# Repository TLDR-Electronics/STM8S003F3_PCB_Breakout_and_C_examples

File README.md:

# STM8S003F3 PCB Breakout and C examples
Breakout board and some lightweight C examples of the STM8S003F3 using the Small Device C Compiler (SDCC). Without the need for the STM8S/A Standard peripheral library.
Some examples are also compatable with the IAR compiler.

Gerbers and design files for low cost breakout boards for the STM8S003F3 are available in the hardware folder.
The breakout boards are designed in EasyEDA and KiCAD are placed in the hardware folder. 
The EasyEDA gerbers and assembly files have been phyically tested with JLCPCB. KiCAD files have not been tested.

## Software Setup
To compile and run this SDCC will need to be installed.
On linux, this can be done with the `sudo apt update` and `sudo apt install sdcc`

## Flashing the STM8
The stm8flash utility is used to program the stm8 devices: https://github.com/vdudouyt/stm8flash 
Make sure you have an compatable ST-LINK programmer
This will need to be compiled. The directory for the executable was placed in:

>/home/*\<your username\>*/tools/stm8flash/

## Make Commands

Typing in the following commands in the development folder:
- `make blink` will compile the blink program to the *./bin/* folder.
- `make tim2` will compile the timer2 interrupt program to the *./bin/* folder.
- `make t2delay` will compile the timer2 delay program to the *./bin/* folder.
- `make burn` command will flash the device depending on the last build.
- `make clean` will clear the binary and the *./bin/* folder.

Depending on your programmer, the makefile may need to be edited.

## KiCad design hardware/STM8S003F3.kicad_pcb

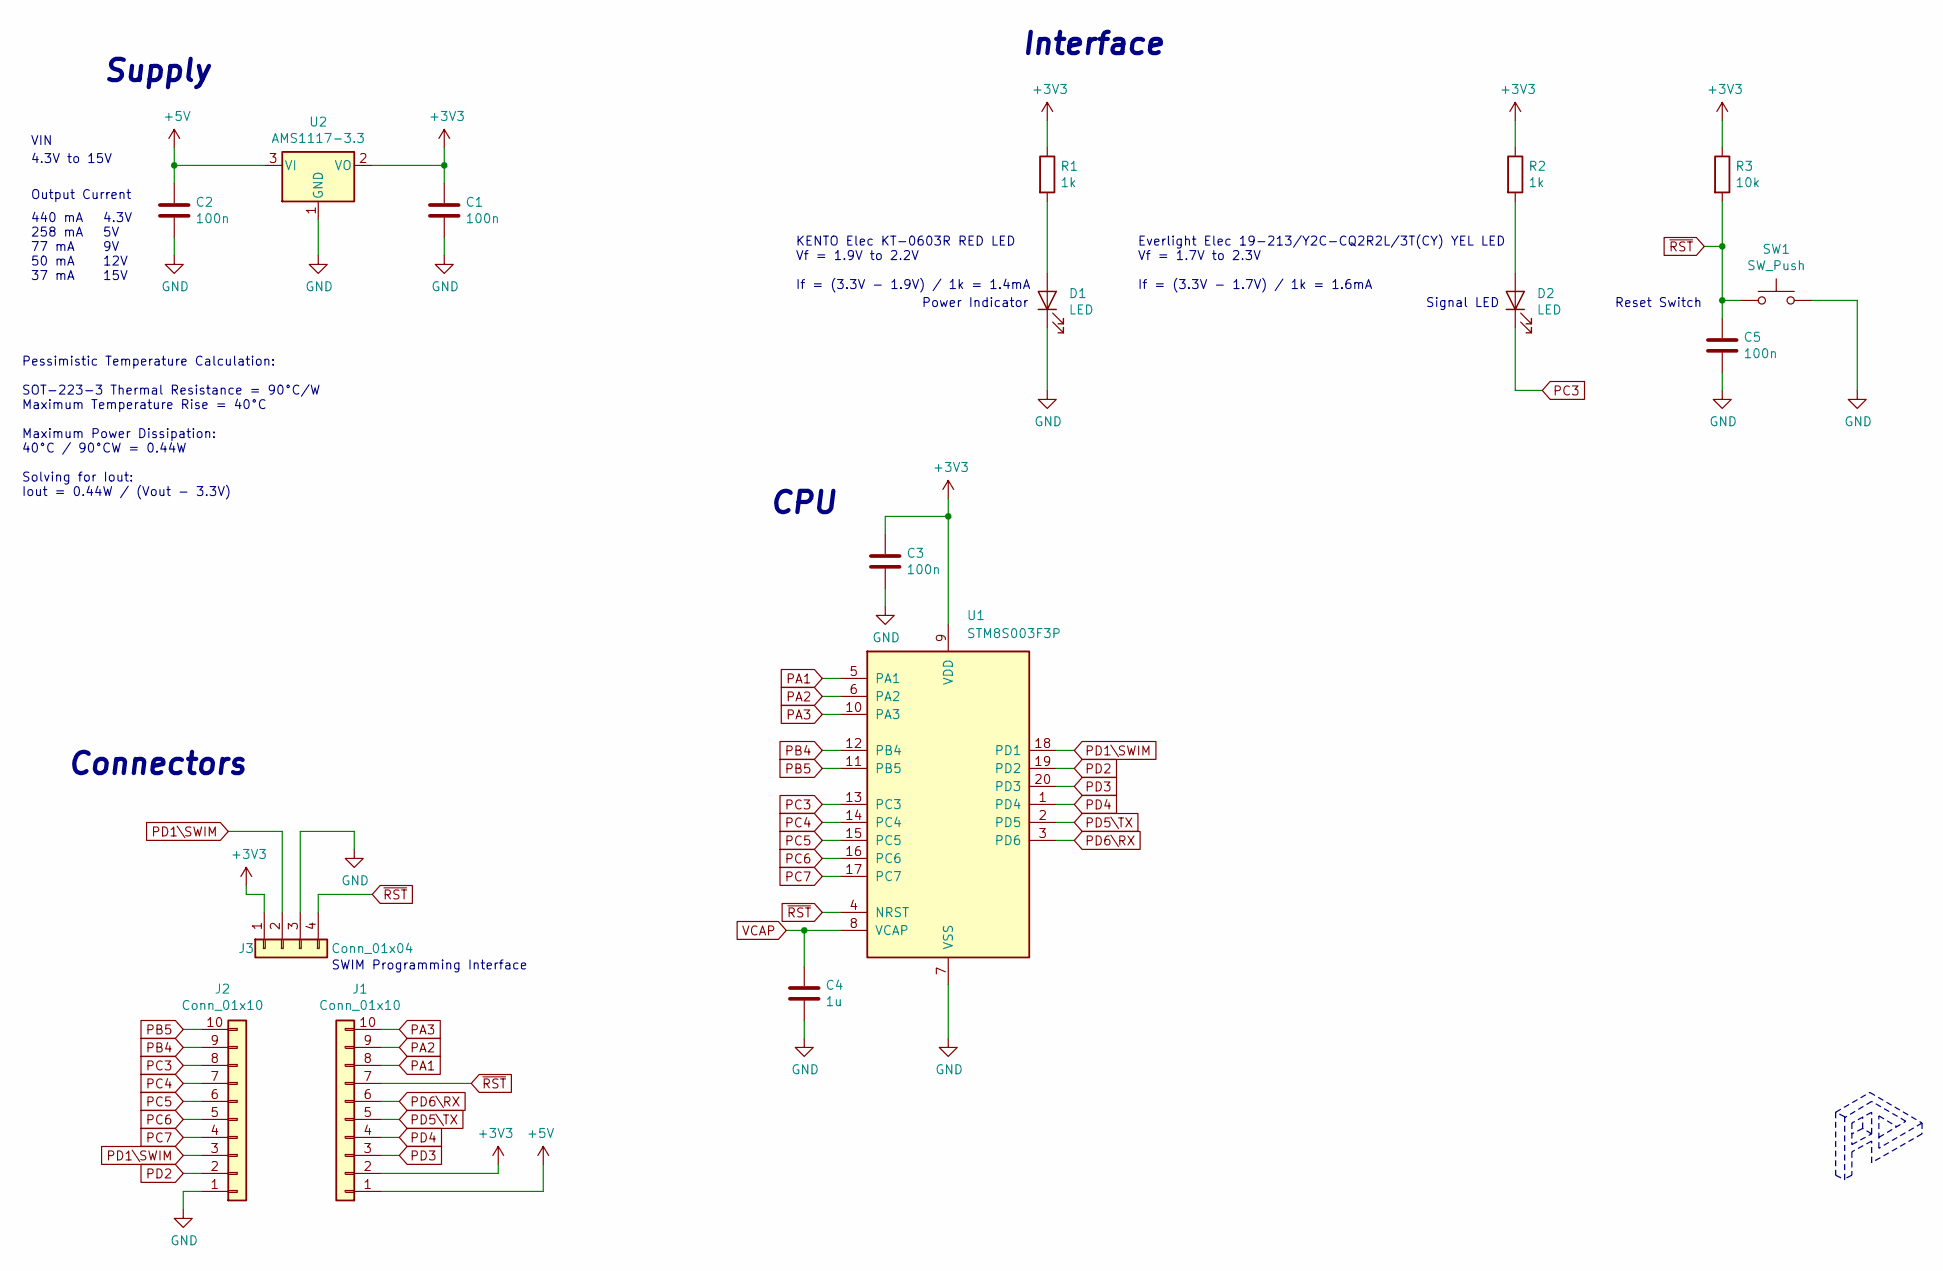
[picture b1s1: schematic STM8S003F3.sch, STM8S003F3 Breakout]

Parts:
C1, C3, C5: 100n; C_0402_1005Metric; LCSC C1525
C2: 100n; C_0603_1608Metric; LCSC C14663
C4: 1u; C_0402_1005Metric; LCSC C52923
D1: LED; LED_0603_1608Metric; LCSC C2286
D2: LED; LED_0603_1608Metric; LCSC C72038
J1, J2: Conn_01x10; PinHeader_1x10_P2.54mm_Vertical
J3: Conn_01x04; PinHeader_1x04_P2.54mm_Vertical
R1, R2: 1k; R_0402_1005Metric; LCSC C11702
R3: 10k; R_0402_1005Metric; LCSC C25744
SW1: SW_Push; SW_SPST_CK_RS282G05A3; LCSC C118141
U1: STM8S003F3P; TSSOP-20_4.4x6.5mm_P0.65mm; LCSC C52717
U2: AMS1117-3.3; SOT-223-3_TabPin2; LCSC C6186

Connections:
+3V3: C1.1, C3.1, J1.2, J3.1, R1.1, R2.1, R3.1, U1.9 (VDD), U2.2 (VO)
+5V: C2.1, J1.1, U2.3 (VI)
GND: C1.2, C2.2, C3.2, C4.2, C5.2, D1.1 (K), J2.1, J3.3, SW1.2, U1.7 (VSS), U2.1 (GND)
unnamed: D1.2 (A), R1.2
unnamed: D2.2 (A), R2.2
PA1: J1.8, U1.5 (PA1)
PA2: J1.9, U1.6 (PA2)
PA3: J1.10, U1.10 (PA3)
PB4: J2.9, U1.12 (PB4)
PB5: J2.10, U1.11 (PB5)
PC3: D2.1 (K), J2.8, U1.13 (PC3)
PC4: J2.7, U1.14 (PC4)
PC5: J2.6, U1.15 (PC5)
PC6: J2.5, U1.16 (PC6)
PC7: J2.4, U1.17 (PC7)
PD1\SWIM: J2.3, J3.2, U1.18 (PD1)
PD2: J2.2, U1.19 (PD2)
PD3: J1.3, U1.20 (PD3)
PD4: J1.4, U1.1 (PD4)
PD5\TX: J1.5, U1.2 (PD5)
PD6\RX: J1.6, U1.3 (PD6)
VCAP: C4.1, U1.8 (VCAP)
~RST: C5.1, J1.7, J3.4, R3.2, SW1.1, U1.4 (NRST)

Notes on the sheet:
Connectors
Supply
Interface
Power Indicator
Signal LED
Reset Switch
CPU
SWIM Programming Interface
Pessimistic Temperature Calculation: SOT-223-3 Thermal Resistance = 90°C/W Maximum Temperature Rise = 40°C Maximum Power Dissipation: 40°C / 90°CW = 0.44W Solving for Iout: Iout = 0.44W / (Vout - 3.3V)
4.3V to 15V
4.3V 5V 9V 12V 15V
440 mA 258 mA 77 mA 50 mA 37 mA
VIN
Output Current
KENTO Elec KT-0603R RED LED Vf = 1.9V to 2.2V If = (3.3V - 1.9V) / 1k = 1.4mA
Everlight Elec 19-213/Y2C-CQ2R2L/3T(CY) YEL LED Vf = 1.7V to 2.3V If = (3.3V - 1.7V) / 1k = 1.6mA

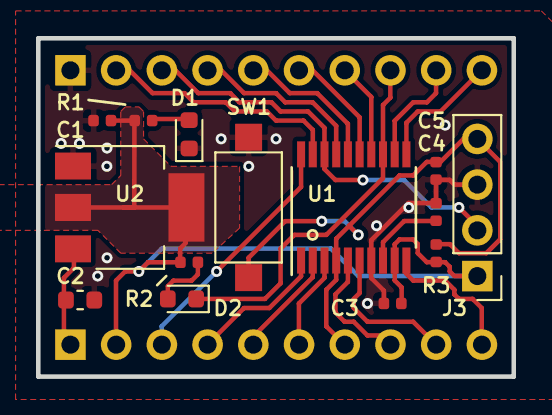
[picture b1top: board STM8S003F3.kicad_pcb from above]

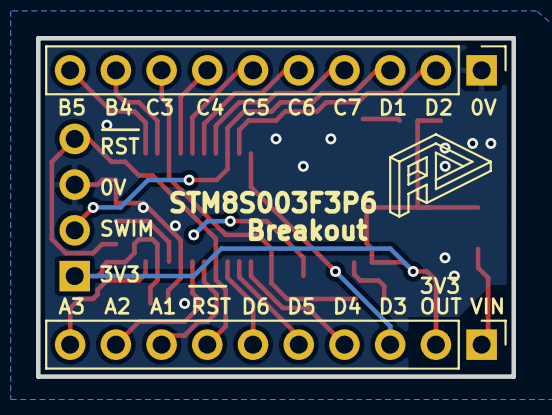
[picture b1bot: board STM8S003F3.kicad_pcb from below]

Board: 2 copper layers, 26.4 x 18.8 mm, 16 parts (2 on the bottom side), 23 nets.

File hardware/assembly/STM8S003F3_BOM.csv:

Designator,Quantity,Value,Footprint,LCSC Part #
"C1, C3, C5, ",3,100n,Capacitor_SMD:C_0402_1005Metric,C1525
"C2, ",1,100n,Capacitor_SMD:C_0603_1608Metric,C14663
"C4, ",1,1u,Capacitor_SMD:C_0402_1005Metric,C52923
"D1, ",1,LED,LED_SMD:LED_0603_1608Metric,C2286
D2,1,LED,LED_SMD:LED_0603_1608Metric,C72038
"R1, R2, ",2,1k,Resistor_SMD:R_0402_1005Metric,C11702
"R3, ",1,10k,Resistor_SMD:R_0402_1005Metric,C25744
"SW1, ",1,SW_Push,Button_Switch_SMD:SW_SPST_CK_RS282G05A3,C118141
"U1, ",1,STM8S003F3P,Package_SO:TSSOP-20_4.4x6.5mm_P0.65mm,C52717
"U2, ",1,AMS1117-3.3,Package_TO_SOT_SMD:SOT-223-3_TabPin2,C6186

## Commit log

2020-08-07 Added a TIM2 interrupt example
2020-08-08 Create LICENSE
2020-08-08 Added TIM2 delayMs and delayUs example
2020-08-08 updated comments
2020-08-21 Added EasyEDA and KiCad breakout board files
